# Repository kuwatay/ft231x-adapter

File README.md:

# ft231x-adapter
Yet another FT231X-based USB-Serial adapter board with 7pin interface.

There are two versions; One has micro USB jack. The other has Standard type B.

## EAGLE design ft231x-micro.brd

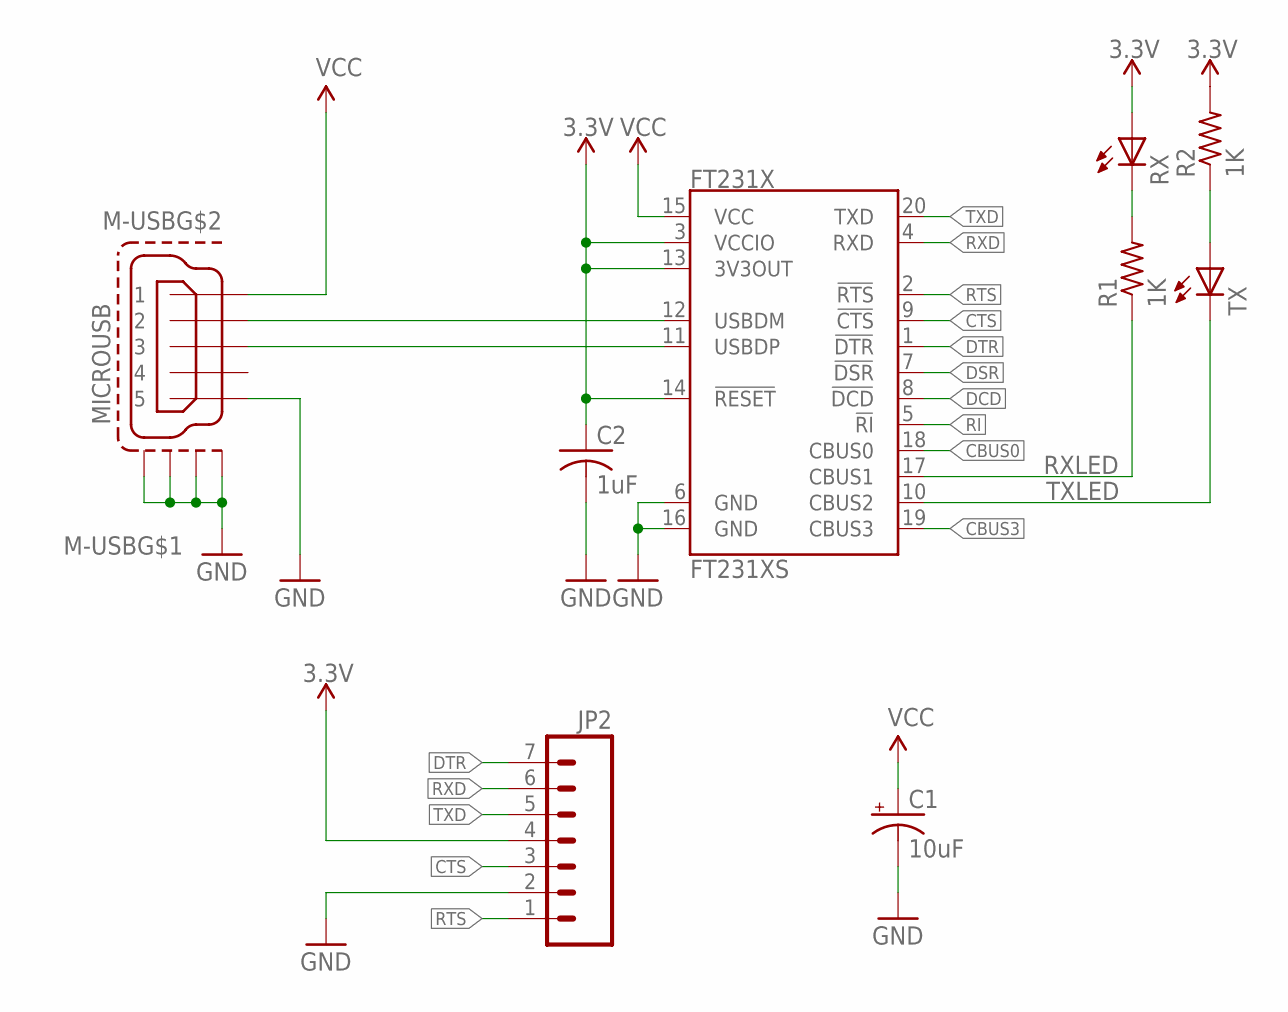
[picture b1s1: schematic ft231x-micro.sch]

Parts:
C1: 10uF; EIA3216
C2: 1uF; C0805
FT231X: FT231XS; SSOP20_L
JP2: M07; 1X07
M-USB: MICROUSB; ZX62R-B-5P
R1, R2: 1K; R0603
RX: LEDCHIP-LED0805; CHIP-LED0805
TX: LEDCHIP-LED0805; CHIP-LED0805

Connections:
3.3V: C2.1, FT231X.3 (VCCIO), FT231X.13 (3V3OUT), FT231X.14 (!RESET), JP2.4, R2.2, RX.A
CBUS0: FT231X.18 (CBUS0)
CBUS3: FT231X.19 (CBUS3)
CTS: FT231X.9 (!CTS), JP2.3
DCD: FT231X.8 (!DCD)
DSR: FT231X.7 (!DSR)
DTR: FT231X.1 (!DTR), JP2.7
GND: C1.C (-), C2.2, FT231X.6 (GND), FT231X.16 (GND), JP2.2, M-USB.5, M-USB.M1 (S1), M-USB.M2 (S2), M-USB.M3 (S3), M-USB.M4 (S4)
unnamed: R2.1, TX.A
unnamed: FT231X.11 (USBDP), M-USB.3
unnamed: FT231X.12 (USBDM), M-USB.2
unnamed: R1.2, RX.C
RI: FT231X.5 (!RI)
RTS: FT231X.2 (!RTS), JP2.1
RXD: FT231X.4 (RXD), JP2.6
RXLED: FT231X.17 (CBUS1), R1.1
TXD: FT231X.20 (TXD), JP2.5
TXLED: FT231X.10 (CBUS2), TX.C
VCC: C1.A (+), FT231X.15 (VCC), M-USB.1

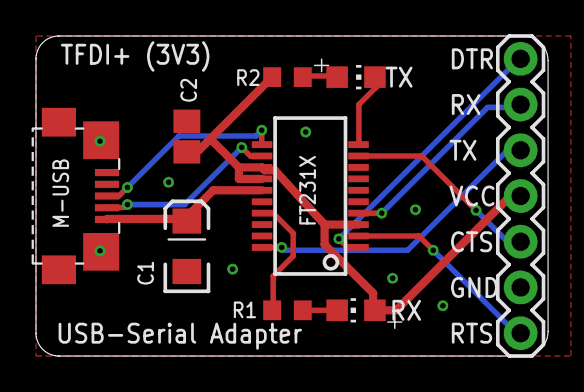
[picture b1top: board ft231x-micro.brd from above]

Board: 2 copper layers, 28.4 x 17.8 mm, 9 parts (0 on the bottom side), 14 nets.

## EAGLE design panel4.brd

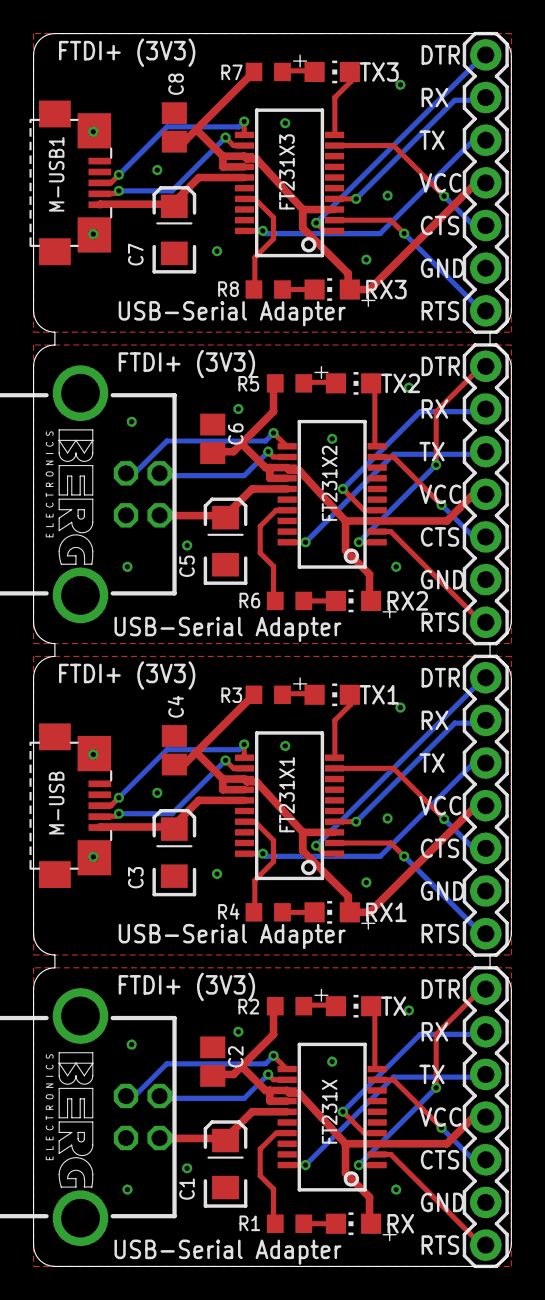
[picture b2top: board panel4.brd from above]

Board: 2 copper layers, 28.4 x 73.4 mm, 36 parts (0 on the bottom side), 56 nets.

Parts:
C1, C3, C5, C7: 10uF; EIA3216
C2, C4, C6, C8: 1uF; C0805
FT231X, FT231X1, FT231X2, FT231X3: FT231XS; SSOP20_L
JP1, JP2, JP3, JP4: 1X07
M-USB, M-USB1: MICROUSB; ZX62R-B-5P
R1, R2, R3, R4, R5, R6, R7, R8: 1K; R0603
RX, RX1, RX2, RX3: CHIP-LED0805
TX, TX1, TX2, TX3: CHIP-LED0805
X1, X2: PN61729-S

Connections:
3.3V: C2.1, FT231X.3, FT231X.13, FT231X.14, JP2.4, R2.2, RX.A
3.3V1: C4.1, FT231X1.3, FT231X1.13, FT231X1.14, JP1.4, R3.2, RX1.A
3.3V2: C6.1, FT231X2.3, FT231X2.13, FT231X2.14, JP3.4, R5.2, RX2.A
3.3V3: C8.1, FT231X3.3, FT231X3.13, FT231X3.14, JP4.4, R7.2, RX3.A
CTS: FT231X.9, JP2.3
CTS1: FT231X1.9, JP1.3
CTS2: FT231X2.9, JP3.3
CTS3: FT231X3.9, JP4.3
DTR: FT231X.1, JP2.7
DTR1: FT231X1.1, JP1.7
DTR2: FT231X2.1, JP3.7
DTR3: FT231X3.1, JP4.7
GND: C1.C, C2.2, FT231X.6, FT231X.16, JP2.2, X1.4, X1.S1, X1.S2
GND1: C3.C, C4.2, FT231X1.6, FT231X1.16, JP1.2, M-USB.5, M-USB.M1, M-USB.M2, M-USB.M3, M-USB.M4
GND2: C7.C, C8.2, FT231X3.6, FT231X3.16, JP4.2, M-USB1.5, M-USB1.M1, M-USB1.M2, M-USB1.M3, M-USB1.M4
GND3: C5.C, C6.2, FT231X2.6, FT231X2.16, JP3.2, X2.4, X2.S1, X2.S2
unnamed: R2.1, TX.A
unnamed: FT231X1.11, M-USB.3
unnamed: FT231X.11, X1.3
unnamed: FT231X.12, X1.2
unnamed: FT231X1.12, M-USB.2
unnamed: R1.2, RX.C
unnamed: R4.2, RX1.C
unnamed: R3.1, TX1.A
unnamed: FT231X2.11, X2.3
unnamed: FT231X2.12, X2.2
unnamed: R6.2, RX2.C
unnamed: R5.1, TX2.A
unnamed: FT231X3.11, M-USB1.3
unnamed: FT231X3.12, M-USB1.2
unnamed: R8.2, RX3.C
unnamed: R7.1, TX3.A
RTS: FT231X.2, JP2.1
RTS1: FT231X1.2, JP1.1
RTS2: FT231X2.2, JP3.1
RTS3: FT231X3.2, JP4.1
RXD: FT231X.4, JP2.6
RXD1: FT231X1.4, JP1.6
RXD2: FT231X2.4, JP3.6
RXD3: FT231X3.4, JP4.6
RXLED: FT231X.17, R1.1
RXLED1: FT231X1.17, R4.1
RXLED2: FT231X2.17, R6.1
RXLED3: FT231X3.17, R8.1
TXD: FT231X.20, JP2.5
TXD1: FT231X1.20, JP1.5
TXD2: FT231X2.20, JP3.5
TXD3: FT231X3.20, JP4.5
TXLED: FT231X.10, TX.C
TXLED1: FT231X1.10, TX1.C
TXLED2: FT231X2.10, TX2.C
TXLED3: FT231X3.10, TX3.C
VCC: C1.A, FT231X.15, X1.1
VCC1: C3.A, FT231X1.15, M-USB.1
VCC2: C5.A, FT231X2.15, X2.1
VCC3: C7.A, FT231X3.15, M-USB1.1

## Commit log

2017-08-19 add README

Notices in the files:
parts and their libraries:
SparkFun-DigitalIC: Licensing: CC v3.0 Share-Alike You are welcome to use this library for commercial purposes.
